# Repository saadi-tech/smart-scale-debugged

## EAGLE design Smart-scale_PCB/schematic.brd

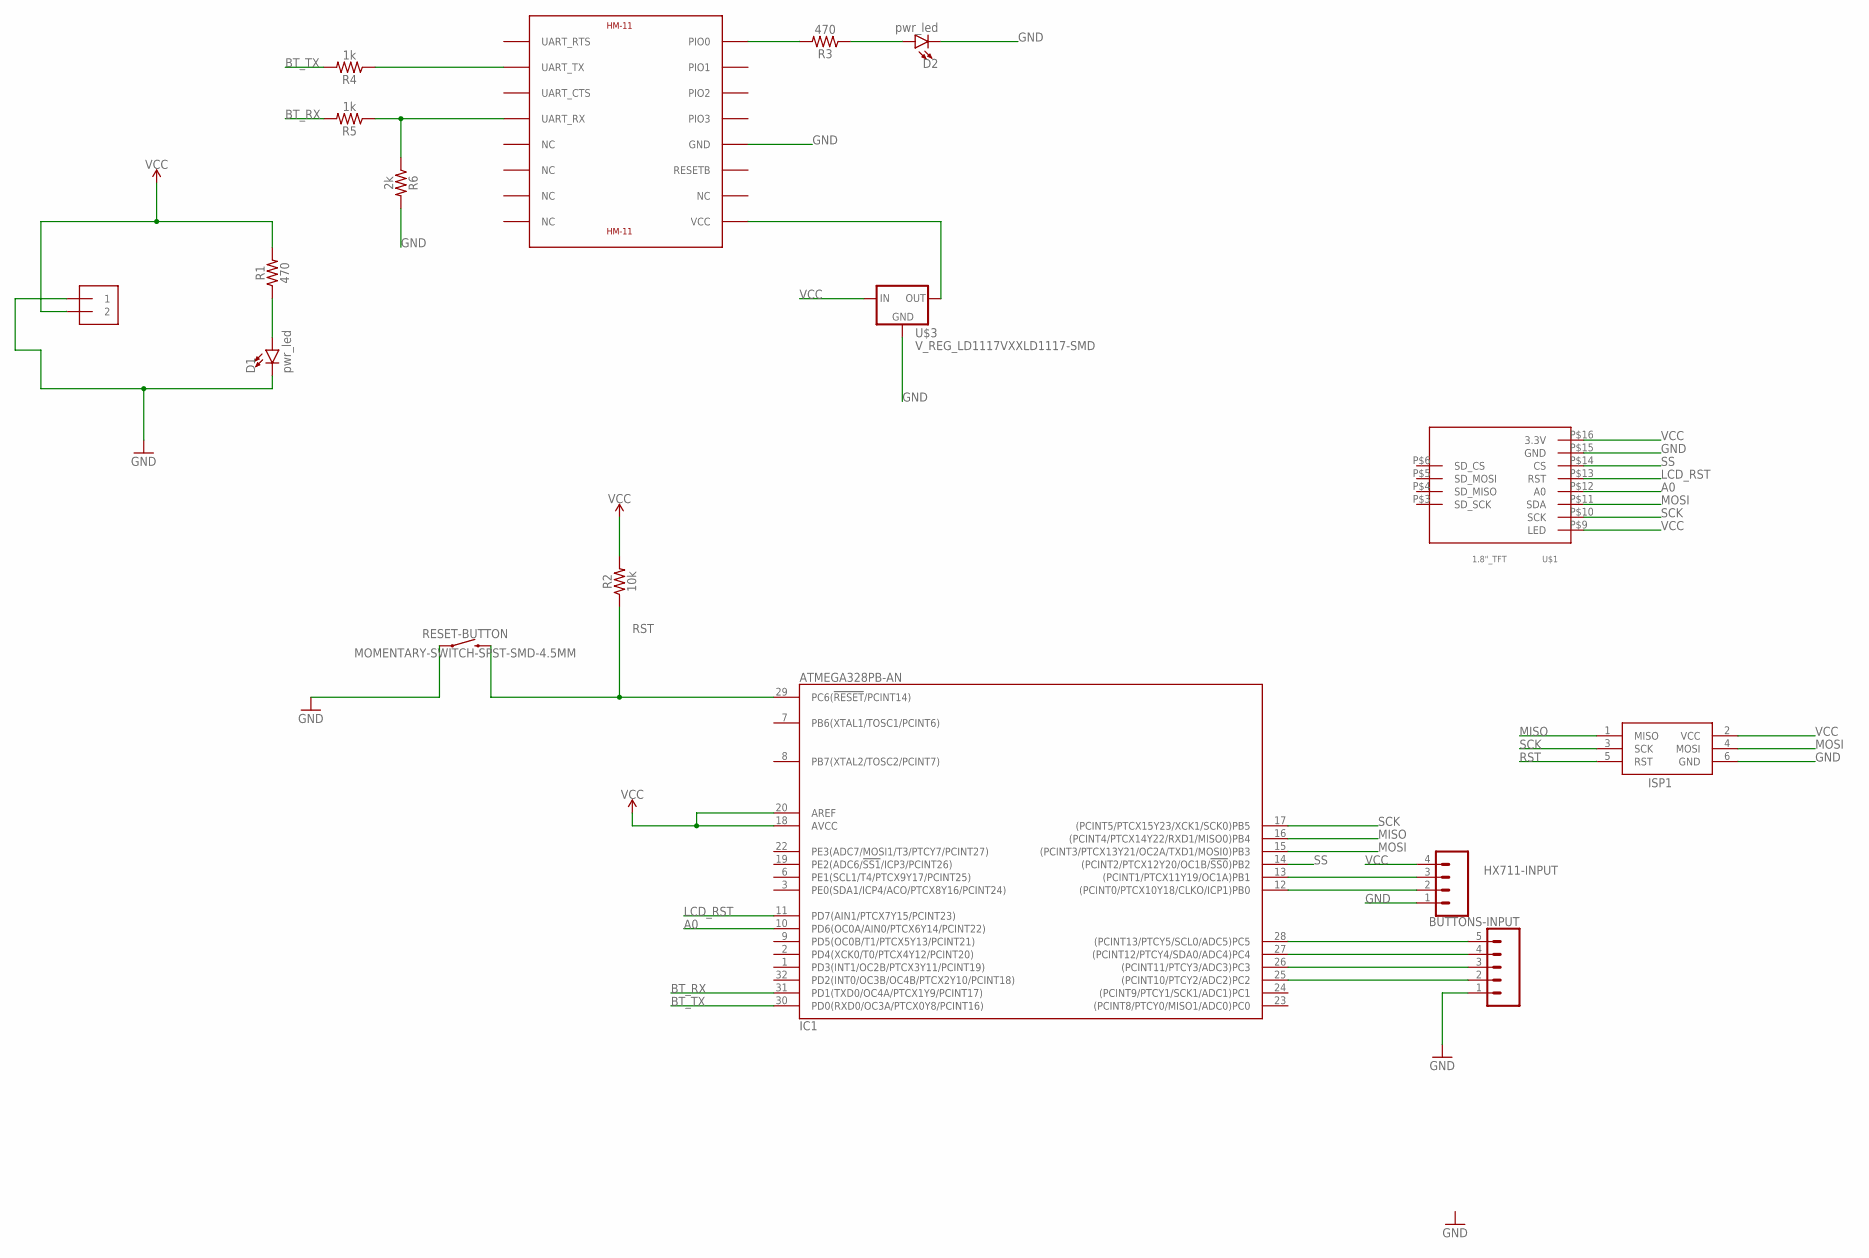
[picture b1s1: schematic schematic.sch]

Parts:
BUTTONS-INPUT: CONN_05; 1X05
D1, D2: pwr_led; LED-1206
HX711-INPUT: CONN_04LONGPADS; 1X04_LONGPADS
IC1: ATMEGA328PB-AN; QFP32_7X7_0.80
ISP1: AVRISP-BOX
PWR: 1X2-3.5MM
R1, R3: 470; 1206
R2: 10k; 1206
R4, R5: 1k; 1206
R6: 2k; 1206
RESET-BUTTON: MOMENTARY-SWITCH-SPST-SMD-4.5MM; TACTILE_SWITCH_SMD_4.5MM
U$1: 1.8"_TFT
U$2: HM-11
U$3: V_REG_LD1117VXXLD1117-SMD; SOT223

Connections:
A0: IC1.10 (PD6(OC0A/AIN0/PTCX6Y14/PCINT22)), U$1.P$12 (A0)
BT_RX: IC1.31 (PD1(TXD0/OC4A/PTCX1Y9/PCINT17)), R5.2
BT_TX: IC1.30 (PD0(RXD0/OC3A/PTCX0Y8/PCINT16)), R4.2
GND: BUTTONS-INPUT.1, D1.C, D2.C, HX711-INPUT.1, IC1.5 (GND), IC1.21 (GND), ISP1.6 (GND), PWR.1, R6.2, RESET-BUTTON.2 (1), RESET-BUTTON.3 (1), U$1.P$15 (GND), U$2.GND, U$3.1 (GND)
LCD_RST: IC1.11 (PD7(AIN1/PTCX7Y15/PCINT23)), U$1.P$13 (RST)
MISO: IC1.16 ((PCINT4/PTCX14Y22/RXD1/MISO0)PB4), ISP1.1 (MISO)
MOSI: IC1.15 ((PCINT3/PTCX13Y21/OC2A/TXD1/MOSI0)PB3), ISP1.4 (MOSI), U$1.P$11 (SDA)
unnamed: U$2.VCC, U$3.2 (OUT)
unnamed: BUTTONS-INPUT.5, IC1.28 ((PCINT13/PTCY5/SCL0/ADC5)PC5)
unnamed: D1.A, R1.1
unnamed: BUTTONS-INPUT.4, IC1.27 ((PCINT12/PTCY4/SDA0/ADC4)PC4)
unnamed: BUTTONS-INPUT.3, IC1.26 ((PCINT11/PTCY3/ADC3)PC3)
unnamed: BUTTONS-INPUT.2, IC1.25 ((PCINT10/PTCY2/ADC2)PC2)
unnamed: HX711-INPUT.2, IC1.12 ((PCINT0/PTCX10Y18/CLKO/ICP1)PB0)
unnamed: HX711-INPUT.3, IC1.13 ((PCINT1/PTCX11Y19/OC1A)PB1)
unnamed: R3.2, U$2.PIO0
unnamed: D2.A, R3.1
unnamed: R4.1, U$2.UART_TX
unnamed: R5.1, R6.1, U$2.UART_RX
RST: IC1.29 (PC6(!RESET!/PCINT14)), ISP1.5 (RST), R2.1, RESET-BUTTON.1 (2), RESET-BUTTON.4 (2)
SCK: IC1.17 ((PCINT5/PTCX15Y23/XCK1/SCK0)PB5), ISP1.3 (SCK), U$1.P$10 (SCK)
SS: IC1.14 ((PCINT2/PTCX12Y20/OC1B/!SS0!)PB2), U$1.P$14 (CS)
VCC: HX711-INPUT.4, IC1.4 (VCC), IC1.18 (AVCC), IC1.20 (AREF), ISP1.2 (VCC), PWR.2, R1.2, R2.2, U$1.P$9 (LED), U$1.P$16 (3.3V), U$3.3 (IN)

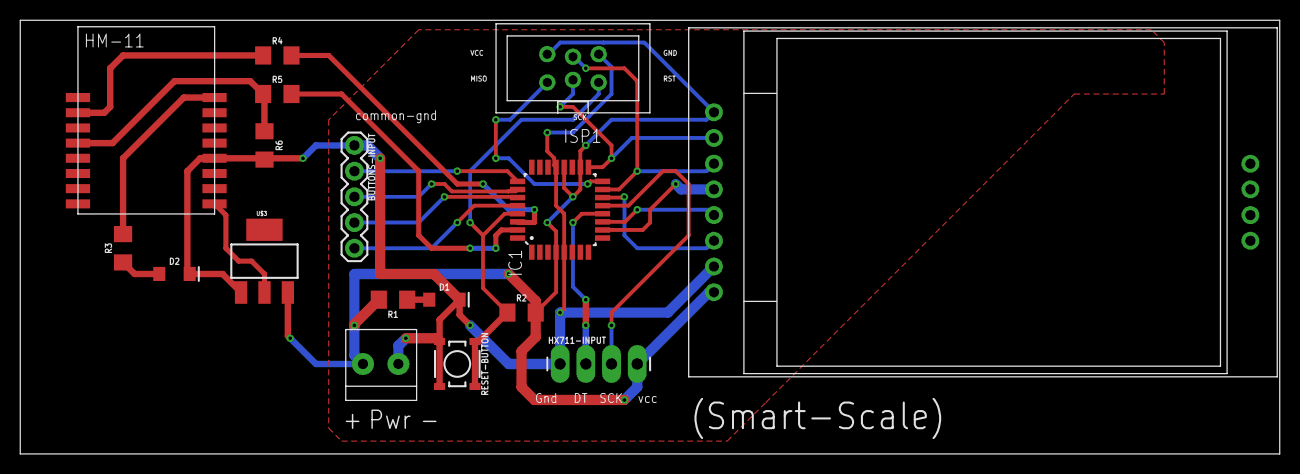
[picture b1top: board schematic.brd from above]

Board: 2 copper layers, 124.4 x 42.9 mm, 17 parts (0 on the bottom side), 23 nets.

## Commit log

2020-11-11 ding weight with GUI
2020-11-17 C:\Users\GAndoo\Desktop\Smart_Scale (sensor_debuggingB design is ready

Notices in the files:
parts and their libraries:
SparkFun-Connectors: Licensing: Creative Commons ShareAlike 4.0 International - https://creativecommons.org/licenses/by-sa/4.0
